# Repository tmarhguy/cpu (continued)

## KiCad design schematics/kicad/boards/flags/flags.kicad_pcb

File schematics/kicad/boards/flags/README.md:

# Flags Generation Board

**Comparison and status flag generation**

---

## Function

Generate 4 flags for ALU status and comparison:
- **LESS:** A < B (magnitude comparison)
- **EQUAL:** A == B (equality check)
- **POSITIVE:** OUT > 0 (positive result)
- **COUT:** Carry out (from adder)

---

## Schematic

*Flags generation circuit*

---

## Flag Implementations

### EQUAL Flag (~100T)

**Function:** Detect A == B

**Logic:**
```
EQUAL = ~((A[7] XOR B[7]) | (A[6] XOR B[6]) | ... | (A[0] XOR B[0]))
```

**Implementation:**
- 8× XOR gates (96T)
- 8-input NOR gate (16T)

### LESS Flag (~120T)

**Function:** Detect A < B

**Logic:** Cascaded priority comparison (MSB first)

**Implementation:** ~120T comparator logic

### POSITIVE Flag (~20T)

**Function:** Detect OUT > 0

**Logic:**
```
NOT_ZERO = OUT[7] | ... | OUT[0]
POSITIVE = ~OUT[7] & NOT_ZERO
```

### COUT Flag (0T)

**Function:** Pass carry from adder

**Implementation:** Direct wire

---

## Signals

**Inputs:**
- A[7:0], B[7:0] - For comparison
- OUT[7:0] - For POSITIVE detection
- COUT_IN - From adder

**Outputs:**
- LESS, EQUAL, POSITIVE, COUT

---

**Last Updated:** 2026-01-16

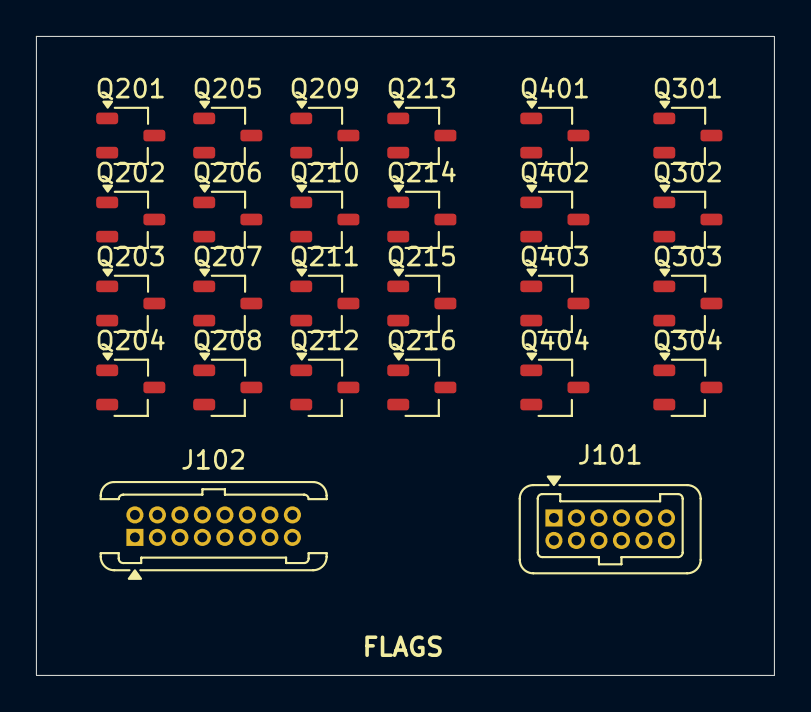
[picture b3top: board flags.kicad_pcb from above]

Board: 2 copper layers, 41.0 x 35.5 mm, 26 parts (0 on the bottom side), 23 nets, no tracks yet.

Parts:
J101: Conn_01x12_Pin; Harwin_Gecko-G125-FVX1205L0X_2x06_P1.25mm_Vertical
J102: Conn_01x16_Pin; Harwin_Gecko-G125-MVX1605L0X_2x08_P1.25mm_Vertical
Q201, Q210, Q211, Q212, Q213, Q214, Q215, Q216, Q301, Q304, Q401, Q404: NMOS; TSOT-23
Q202, Q203, Q204, Q205, Q206, Q207, Q208, Q209, Q302, Q303, Q402, Q403: PMOS; TSOT-23

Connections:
/SUM0: Q201.2 (G), Q202.2 (G)
/SUM1: Q203.2 (G), Q210.2 (G)
/SUM2: Q204.2 (G), Q211.2 (G)
/SUM3: Q205.2 (G), Q212.2 (G)
/SUM4: Q206.2 (G), Q213.2 (G)
/SUM5: Q207.2 (G), Q214.2 (G)
/SUM6: Q208.2 (G), Q215.2 (G)
/SUM7: Q209.2 (G), Q216.2 (G)
CMP0: Q301.1 (D), Q303.1 (D), Q304.1 (D), Q403.2 (G), Q404.2 (G)
CMP1: Q201.1 (D), Q209.1 (D), Q210.1 (D), Q211.1 (D), Q212.1 (D), Q213.1 (D), Q214.1 (D), Q215.1 (D), Q216.1 (D), Q301.2 (G), Q302.2 (G), Q401.2 (G), Q402.2 (G)
CMP2: Q401.1 (D), Q403.1 (D), Q404.1 (D)
CMP3: Q201.3 (S), Q210.3 (S), Q211.3 (S), Q212.3 (S), Q213.3 (S), Q214.3 (S), Q215.3 (S), Q216.3 (S), Q301.3 (S), Q304.3 (S), Q401.3 (S), Q404.3 (S)
C_OUT: Q303.2 (G), Q304.2 (G)
unnamed: Q202.1 (D), Q203.3 (S)
unnamed: Q203.1 (D), Q204.3 (S)
unnamed: Q204.1 (D), Q205.3 (S)
unnamed: Q205.1 (D), Q206.3 (S)
unnamed: Q206.1 (D), Q207.3 (S)
unnamed: Q207.1 (D), Q208.3 (S)
unnamed: Q208.1 (D), Q209.3 (S)
unnamed: Q302.1 (D), Q303.3 (S)
unnamed: Q402.1 (D), Q403.3 (S)
VCC: Q202.3 (S), Q302.3 (S), Q402.3 (S)

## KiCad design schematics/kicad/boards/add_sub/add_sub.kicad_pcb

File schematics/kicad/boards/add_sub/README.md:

# Add/Subtract Module

**8-bit adder with conditional B inversion for subtraction**

---

## Function

Implements both addition and subtraction using a single 8-bit ripple-carry adder.

**Operations:**
- ADD: OUT = A + B (when M=0)
- SUB: OUT = A - B (when M=1, using 2's complement)

---

## Block Diagram

```
A[7:0] ────────────────┐
                       ├──> Full Adder (8-bit) ──> SUM[7:0]
B[7:0] ──> XOR[M] ─────┤
                       │
M ──────────────> Cin ─┘
```

---

## Implementation

### XOR Array (96T)

**Purpose:** Conditional B inversion

```
B'[i] = B[i] XOR M  (for i = 0 to 7)
```

**Truth table:**
| M | B | B' |
|---|---|----|
| 0 | 0 | 0 |
| 0 | 1 | 1 |
| 1 | 0 | 1 |
| 1 | 1 | 0 |

When M=0 (ADD): B' = B  
When M=1 (SUB): B' = ~B

### 8-Bit Ripple-Carry Adder (336T)

**Structure:** 8 cascaded full adders

**Per full adder (42T):**
- Sum = A ⊕ B' ⊕ Cin
- Cout = A·B' + Cin·(A ⊕ B')

---

## Schematic

*Complete add/subtract module schematic*

> **Evidence:** Schematic shows XOR array and 8-bit adder.

---

## PCB

*Fabricated add/subtract board*

> **Evidence:** Physical implementation of arithmetic unit.

---

## Signals

### Inputs

| Signal | Width | Voltage | Description |
|--------|-------|---------|-------------|
| A[7:0] | 8 bits | 0V/5V | First operand |
| B[7:0] | 8 bits | 0V/5V | Second operand |
| M | 1 bit | 0V/5V | ADD(0) or SUB(1) mode |
| VCC | Power | 5V | Power supply |
| GND | Power | 0V | Ground |

### Outputs

| Signal | Width | Voltage | Description |
|--------|-------|---------|-------------|
| SUM[7:0] | 8 bits | 0V/5V | Arithmetic result |
| COUT | 1 bit | 0V/5V | Carry out (unsigned overflow) |

---

## Timing

**Propagation delay:**
- XOR array: ~15ns
- Adder (worst case): ~400ns
- **Total:** ~415ns (input to output)

**Critical path:** A[0] → XOR → FA0 → FA1 → ... → FA7 → SUM[7]

---

## Testing

**Test vectors:**

| A | B | M | Expected SUM | Expected COUT |
|---|---|---|--------------|---------------|
| 0x01 | 0x01 | 0 | 0x02 | 0 |
| 0xFF | 0x01 | 0 | 0x00 | 1 |
| 0x64 | 0x23 | 1 | 0x41 | 1 |
| 0x00 | 0x01 | 1 | 0xFF | 0 |

---

**Last Updated:** 2026-01-16

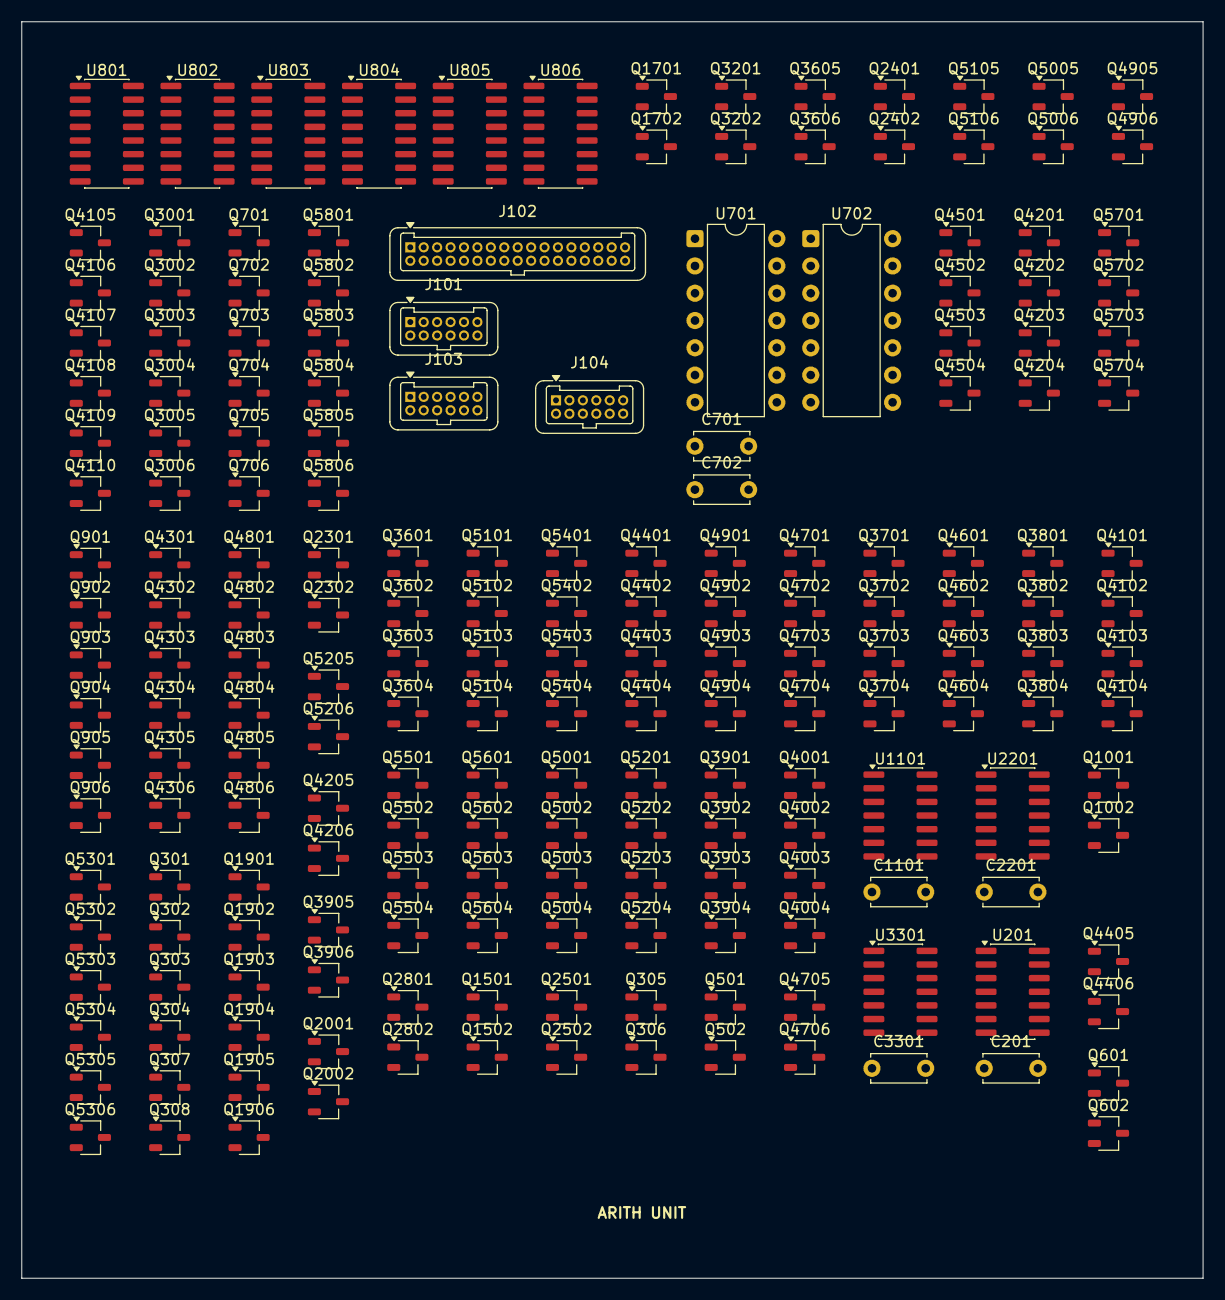
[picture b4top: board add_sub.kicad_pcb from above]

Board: 2 copper layers, 110.0 x 117.0 mm, 200 parts (0 on the bottom side), 148 nets, no tracks yet.

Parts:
C201, C701, C702, C1101, C2201, C3301: 100nF; C_Disc_D5.0mm_W2.5mm_P5.00mm
J101, J103, J104: Conn_01x12_Pin; Harwin_Gecko-G125-FVX1205L0X_2x06_P1.25mm_Vertical
J102: Conn_01x34_Pin; Harwin_Gecko-G125-FVX3405L0X_2x17_P1.25mm_Vertical
Q301, Q304, Q306, Q308, Q502, Q602, Q701, Q704, Q706, Q901, Q904, Q906, Q1002, Q1502, Q1702, Q1901, Q1904, Q1906, Q2002, Q2302, Q2402, Q2502, Q2802, Q3001, Q3004, Q3006, Q3202, Q3602, Q3603, Q3606, Q3702, Q3703, Q3802, Q3803, Q3902, Q3903, Q3906, Q4002, Q4003, Q4102, Q4103, Q4105, Q4108, Q4110, Q4202, Q4203, Q4206, Q4301, Q4304, Q4306, Q4402, Q4403, Q4406, Q4502, Q4503, Q4602, Q4603, Q4702, Q4703, Q4706, Q4801, Q4804, Q4806, Q4902, Q4903, Q4906, Q5002, Q5003, Q5006, Q5102, Q5103, Q5106, Q5202, Q5203, Q5206, Q5301, Q5304, Q5306, Q5402, Q5403, Q5502, Q5503, Q5602, Q5603, Q5702, Q5703, Q5801, Q5804, Q5806: NMOS; TSOT-23
Q302, Q303, Q305, Q307, Q501, Q601, Q702, Q703, Q705, Q902, Q903, Q905, Q1001, Q1501, Q1701, Q1902, Q1903, Q1905, Q2001, Q2301, Q2401, Q2501, Q2801, Q3002, Q3003, Q3005, Q3201, Q3601, Q3604, Q3605, Q3701, Q3704, Q3801, Q3804, Q3901, Q3904, Q3905, Q4001, Q4004, Q4101, Q4104, Q4106, Q4107, Q4109, Q4201, Q4204, Q4205, Q4302, Q4303, Q4305, Q4401, Q4404, Q4405, Q4501, Q4504, Q4601, Q4604, Q4701, Q4704, Q4705, Q4802, Q4803, Q4805, Q4901, Q4904, Q4905, Q5001, Q5004, Q5005, Q5101, Q5104, Q5105, Q5201, Q5204, Q5205, Q5302, Q5303, Q5305, Q5401, Q5404, Q5501, Q5504, Q5601, Q5604, Q5701, Q5704, Q5802, Q5803, Q5805: PMOS; TSOT-23
U201, U1101, U2201, U3301: 74HC86; SOIC-14_3.9x8.7mm_P1.27mm
U701, U702: 74HC86; DIP-14_W7.62mm
U801, U802, U803, U804, U805, U806: 74HC157; SOIC-16_3.9x9.9mm_P1.27mm

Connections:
/4to1mux1/B0: U801.3 (I1a), U801.6 (I1b), U801.10 (I1c), U801.13 (I1d), U802.3 (I1a), U802.6 (I1b), U802.10 (I1c)
/4to1mux1/Y0: U701.1, U805.4 (Za)
/4to1mux1/Y1: U701.4, U805.7 (Zb)
/4to1mux1/Y2: U701.9, U805.9 (Zc)
/4to1mux1/Y3: U701.12, U805.12 (Zd)
/4to1mux1/Y4: U702.1, U806.4 (Za)
/4to1mux1/Y5: U702.4, U806.7 (Zb)
/4to1mux1/Y6: U702.9, U806.9 (Zc)
/4to1mux1/Y7: U702.12, U806.12 (Zd)
/B_SEL0: Q4705.1 (D), Q4706.1 (D), U805.1 (S), U806.1 (S)
/B_SEL1: Q5205.1 (D), Q5206.1 (D), U801.1 (S), U802.1 (S), U803.1 (S), U804.1 (S)
/CTRL0: Q903.2 (G), Q904.2 (G), Q3801.2 (G), Q3803.2 (G), Q5105.2 (G), Q5106.2 (G)
/CTRL1: Q303.2 (G), Q304.2 (G), Q3601.2 (G), Q3603.2 (G)
/CTRL2: Q4905.2 (G), Q4906.2 (G)
/CTRL4: Q901.2 (G), Q902.2 (G)
/C_IN: Q307.1 (D), Q308.1 (D), Q3901.2 (G), Q3903.2 (G), U201.5
/M: Q301.2 (G), Q302.2 (G), Q905.1 (D), Q906.1 (D), U701.2, U701.5, U701.10, U701.13, U702.2, U702.5, U702.10, U702.13
/adder8/B0: Q4002.2 (G), Q4004.2 (G), U201.2, U701.3
/adder8/B1: Q4202.2 (G), Q4204.2 (G), U201.10, U701.6
/adder8/B2: Q4502.2 (G), Q4504.2 (G), U701.8, U1101.2
/adder8/B3: Q4702.2 (G), Q4704.2 (G), U701.11, U1101.10
/adder8/B4: Q5002.2 (G), Q5004.2 (G), U702.3, U2201.2
/adder8/B5: Q5202.2 (G), Q5204.2 (G), U702.6, U2201.10
/adder8/B6: Q5502.2 (G), Q5504.2 (G), U702.8, U3301.2
/adder8/B7: Q5702.2 (G), Q5704.2 (G), U702.11, U3301.10
/adder8/adder2_1/C_OUT: Q4305.1 (D), Q4306.1 (D), Q4401.2 (G), Q4403.2 (G), U1101.5
/adder8/adder2_1/and2_1/B: Q3902.2 (G), Q3904.2 (G), U201.3, U201.4
/adder8/adder2_1/and2_1/Y: Q305.1 (D), Q306.1 (D), Q701.2 (G), Q702.2 (G)
/adder8/adder2_1/and2_1/nand2_1/Y: Q305.2 (G), Q306.2 (G), Q3901.1 (D), Q3902.1 (D), Q3904.1 (D)
/adder8/adder2_1/and2_2/Y: Q703.2 (G), Q704.2 (G), Q1001.1 (D), Q1002.1 (D)
/adder8/adder2_1/and2_2/nand2_1/Y: Q1001.2 (G), Q1002.2 (G), Q4001.1 (D), Q4002.1 (D), Q4004.1 (D)
/adder8/adder2_1/and2_3/A: Q705.1 (D), Q706.1 (D), Q4101.2 (G), Q4103.2 (G), U201.13
/adder8/adder2_1/and2_3/B: Q4102.2 (G), Q4104.2 (G), U201.8, U201.12
/adder8/adder2_1/and2_3/Y: Q501.1 (D), Q502.1 (D)
/adder8/adder2_1/and2_3/nand2_1/Y: Q501.2 (G), Q502.2 (G), Q4101.1 (D), Q4102.1 (D), Q4104.1 (D)
/adder8/adder2_1/and2_4/Y: Q601.1 (D), Q602.1 (D), Q4303.2 (G), Q4304.2 (G)
/adder8/adder2_1/and2_4/nand2_1/Y: Q601.2 (G), Q602.2 (G), Q4201.1 (D), Q4202.1 (D), Q4204.1 (D)
/adder8/adder2_1/or2_2/A: Q4301.2 (G), Q4302.2 (G)
/adder8/adder2_2/C_OUT: Q4805.1 (D), Q4806.1 (D), Q4901.2 (G), Q4903.2 (G), U2201.5
/adder8/adder2_2/and2_1/B: Q4402.2 (G), Q4404.2 (G), U1101.3, U1101.4
/adder8/adder2_2/and2_1/Y: Q1701.1 (D), Q1702.1 (D), Q1901.2 (G), Q1902.2 (G)
/adder8/adder2_2/and2_1/nand2_1/Y: Q1701.2 (G), Q1702.2 (G), Q4401.1 (D), Q4402.1 (D), Q4404.1 (D)
/adder8/adder2_2/and2_2/Y: Q1501.1 (D), Q1502.1 (D), Q1903.2 (G), Q1904.2 (G)
/adder8/adder2_2/and2_2/nand2_1/Y: Q1501.2 (G), Q1502.2 (G), Q4501.1 (D), Q4502.1 (D), Q4504.1 (D)
/adder8/adder2_2/and2_3/A: Q1905.1 (D), Q1906.1 (D), Q4601.2 (G), Q4603.2 (G), U1101.13
/adder8/adder2_2/and2_3/B: Q4602.2 (G), Q4604.2 (G), U1101.8, U1101.12
/adder8/adder2_2/and2_3/Y: Q2501.1 (D), Q2502.1 (D)
/adder8/adder2_2/and2_3/nand2_1/Y: Q2501.2 (G), Q2502.2 (G), Q4601.1 (D), Q4602.1 (D), Q4604.1 (D)
/adder8/adder2_2/and2_4/Y: Q2301.1 (D), Q2302.1 (D), Q4803.2 (G), Q4804.2 (G)
/adder8/adder2_2/and2_4/nand2_1/Y: Q2301.2 (G), Q2302.2 (G), Q4701.1 (D), Q4702.1 (D), Q4704.1 (D)
/adder8/adder2_2/or2_2/A: Q4801.2 (G), Q4802.2 (G)
/adder8/adder2_3/C_OUT: Q5305.1 (D), Q5306.1 (D), Q5401.2 (G), Q5403.2 (G), U3301.5
/adder8/adder2_3/and2_1/B: Q4902.2 (G), Q4904.2 (G), U2201.3, U2201.4
/adder8/adder2_3/and2_1/Y: Q2801.1 (D), Q2802.1 (D), Q3001.2 (G), Q3002.2 (G)
/adder8/adder2_3/and2_1/nand2_1/Y: Q2801.2 (G), Q2802.2 (G), Q4901.1 (D), Q4902.1 (D), Q4904.1 (D)
/adder8/adder2_3/and2_2/Y: Q2001.1 (D), Q2002.1 (D), Q3003.2 (G), Q3004.2 (G)
/adder8/adder2_3/and2_2/nand2_1/Y: Q2001.2 (G), Q2002.2 (G), Q5001.1 (D), Q5002.1 (D), Q5004.1 (D)
/adder8/adder2_3/and2_3/A: Q3005.1 (D), Q3006.1 (D), Q5101.2 (G), Q5103.2 (G), U2201.13
/adder8/adder2_3/and2_3/B: Q5102.2 (G), Q5104.2 (G), U2201.8, U2201.12
/adder8/adder2_3/and2_3/Y: Q3201.1 (D), Q3202.1 (D)
/adder8/adder2_3/and2_3/nand2_1/Y: Q3201.2 (G), Q3202.2 (G), Q5101.1 (D), Q5102.1 (D), Q5104.1 (D)
/adder8/adder2_3/and2_4/Y: Q4205.1 (D), Q4206.1 (D), Q5303.2 (G), Q5304.2 (G)
/adder8/adder2_3/and2_4/nand2_1/Y: Q4205.2 (G), Q4206.2 (G), Q5201.1 (D), Q5202.1 (D), Q5204.1 (D)
/adder8/adder2_3/or2_2/A: Q5301.2 (G), Q5302.2 (G)
/adder8/adder2_4/and2_1/B: Q5402.2 (G), Q5404.2 (G), U3301.3, U3301.4
/adder8/adder2_4/and2_1/Y: Q3905.1 (D), Q3906.1 (D), Q4105.2 (G), Q4106.2 (G)
/adder8/adder2_4/and2_1/nand2_1/Y: Q3905.2 (G), Q3906.2 (G), Q5401.1 (D), Q5402.1 (D), Q5404.1 (D)
/adder8/adder2_4/and2_2/Y: Q2401.1 (D), Q2402.1 (D), Q4107.2 (G), Q4108.2 (G)
/adder8/adder2_4/and2_2/nand2_1/Y: Q2401.2 (G), Q2402.2 (G), Q5501.1 (D), Q5502.1 (D), Q5504.1 (D)
/adder8/adder2_4/and2_3/A: Q4109.1 (D), Q4110.1 (D), Q5601.2 (G), Q5603.2 (G), U3301.13
/adder8/adder2_4/and2_3/B: Q5602.2 (G), Q5604.2 (G), U3301.8, U3301.12
/adder8/adder2_4/and2_3/Y: Q3605.1 (D), Q3606.1 (D)
/adder8/adder2_4/and2_3/nand2_1/Y: Q3605.2 (G), Q3606.2 (G), Q5601.1 (D), Q5602.1 (D), Q5604.1 (D)
/adder8/adder2_4/and2_4/Y: Q4405.1 (D), Q4406.1 (D), Q5803.2 (G), Q5804.2 (G)
/adder8/adder2_4/and2_4/nand2_1/Y: Q4405.2 (G), Q4406.2 (G), Q5701.1 (D), Q5702.1 (D), Q5704.1 (D)
/adder8/adder2_4/or2_2/A: Q5801.2 (G), Q5802.2 (G)
/and2_1/A: Q3701.2 (G), Q3703.2 (G), Q5105.1 (D), Q5106.1 (D)
/and2_1/B: Q3702.2 (G), Q3704.2 (G), Q3802.2 (G), Q3804.2 (G), Q5005.1 (D), Q5006.1 (D)
/and2_1/nand2_1/Y: Q3701.1 (D), Q3702.1 (D), Q3704.1 (D), Q5205.2 (G), Q5206.2 (G)
/and2_2/nand2_1/Y: Q3801.1 (D), Q3802.1 (D), Q3804.1 (D), Q4705.2 (G), Q4706.2 (G)
/and2_3/B: Q3602.2 (G), Q3604.2 (G), Q4905.1 (D), Q4906.1 (D)
/and2_3/nand2_1/Y: Q3601.1 (D), Q3602.1 (D), Q3604.1 (D), Q5005.2 (G), Q5006.2 (G)
A0: Q4001.2 (G), Q4003.2 (G), U201.1
A1: Q4201.2 (G), Q4203.2 (G), U201.9
A2: Q4501.2 (G), Q4503.2 (G), U1101.1
A3: Q4701.2 (G), Q4703.2 (G), U1101.9
A4: Q5001.2 (G), Q5003.2 (G), U2201.1
A5: Q5201.2 (G), Q5203.2 (G), U2201.9
A6: Q5501.2 (G), Q5503.2 (G), U3301.1
A7: Q5701.2 (G), Q5703.2 (G), U3301.9
C_OUT: Q5805.1 (D), Q5806.1 (D)
GND: C201.2, C701.2, C702.2, C1101.2, C2201.2, C3301.2, Q301.3 (S), Q304.3 (S), Q306.3 (S), Q308.3 (S), Q502.3 (S), Q602.3 (S), Q701.3 (S), Q704.3 (S), Q706.3 (S), Q901.3 (S), Q904.3 (S), Q906.3 (S), Q1002.3 (S), Q1502.3 (S), Q1702.3 (S), Q1901.3 (S), Q1904.3 (S), Q1906.3 (S), Q2002.3 (S), Q2302.3 (S), Q2402.3 (S), Q2502.3 (S), Q2802.3 (S), Q3001.3 (S), Q3004.3 (S), Q3006.3 (S), Q3202.3 (S), Q3603.3 (S), Q3606.3 (S), Q3703.3 (S), Q3803.3 (S), Q3903.3 (S), Q3906.3 (S), Q4003.3 (S), Q4103.3 (S), Q4105.3 (S), Q4108.3 (S), Q4110.3 (S), Q4203.3 (S), Q4206.3 (S), Q4301.3 (S), Q4304.3 (S), Q4306.3 (S), Q4403.3 (S), Q4406.3 (S), Q4503.3 (S), Q4603.3 (S), Q4703.3 (S), Q4706.3 (S), Q4801.3 (S), Q4804.3 (S), Q4806.3 (S), Q4903.3 (S), Q4906.3 (S), Q5003.3 (S), Q5006.3 (S), Q5103.3 (S), Q5106.3 (S), Q5203.3 (S), Q5206.3 (S), Q5301.3 (S), Q5304.3 (S), Q5306.3 (S), Q5403.3 (S), Q5503.3 (S), Q5603.3 (S), Q5703.3 (S), Q5801.3 (S), Q5804.3 (S), Q5806.3 (S), U201.7 (GND), U701.7 (GND), U702.7 (GND), U801.8 (GND), U801.15 (E), U802.8 (GND), U802.15 (E), U803.2 (I0a), U803.3 (I1a), U803.5 (I0b), U803.6 (I1b), U803.8 (GND), U803.10 (I1c), U803.11 (I0c), U803.13 (I1d), U803.14 (I0d), U803.15 (E), U804.2 (I0a), U804.3 (I1a), U804.5 (I0b), U804.6 (I1b), U804.8 (GND), U804.10 (I1c), U804.11 (I0c), U804.13 (I1d), U804.14 (I0d), U804.15 (E), U805.8 (GND), U805.15 (E), U806.8 (GND), U806.15 (E), U1101.7 (GND), U2201.7 (GND), U3301.7 (GND)
unnamed: Q301.1 (D), Q303.1 (D), Q304.1 (D), Q307.2 (G), Q308.2 (G)
unnamed: Q302.1 (D), Q303.3 (S)
unnamed: Q701.1 (D), Q703.1 (D), Q704.1 (D), Q705.2 (G), Q706.2 (G)
unnamed: Q702.1 (D), Q703.3 (S)
unnamed: Q901.1 (D), Q903.1 (D), Q904.1 (D), Q905.2 (G), Q906.2 (G)
unnamed: Q902.1 (D), Q903.3 (S)
unnamed: Q1901.1 (D), Q1903.1 (D), Q1904.1 (D), Q1905.2 (G), Q1906.2 (G)
unnamed: Q1902.1 (D), Q1903.3 (S)
unnamed: Q3001.1 (D), Q3003.1 (D), Q3004.1 (D), Q3005.2 (G), Q3006.2 (G)
unnamed: Q3002.1 (D), Q3003.3 (S)
unnamed: Q3602.3 (S), Q3603.1 (D)
unnamed: Q3702.3 (S), Q3703.1 (D)
unnamed: Q3802.3 (S), Q3803.1 (D)
unnamed: Q3902.3 (S), Q3903.1 (D)
unnamed: Q4002.3 (S), Q4003.1 (D)
unnamed: Q4102.3 (S), Q4103.1 (D)
unnamed: Q4105.1 (D), Q4107.1 (D), Q4108.1 (D), Q4109.2 (G), Q4110.2 (G)
unnamed: Q4106.1 (D), Q4107.3 (S)
unnamed: Q4202.3 (S), Q4203.1 (D)
unnamed: Q4301.1 (D), Q4303.1 (D), Q4304.1 (D), Q4305.2 (G), Q4306.2 (G)
unnamed: Q4302.1 (D), Q4303.3 (S)
unnamed: Q4402.3 (S), Q4403.1 (D)
unnamed: Q4502.3 (S), Q4503.1 (D)
unnamed: Q4602.3 (S), Q4603.1 (D)
unnamed: Q4702.3 (S), Q4703.1 (D)
unnamed: Q4801.1 (D), Q4803.1 (D), Q4804.1 (D), Q4805.2 (G), Q4806.2 (G)
unnamed: Q4802.1 (D), Q4803.3 (S)
unnamed: Q4902.3 (S), Q4903.1 (D)
unnamed: Q5002.3 (S), Q5003.1 (D)
unnamed: Q5102.3 (S), Q5103.1 (D)
unnamed: Q5202.3 (S), Q5203.1 (D)
unnamed: Q5301.1 (D), Q5303.1 (D), Q5304.1 (D), Q5305.2 (G), Q5306.2 (G)
unnamed: Q5302.1 (D), Q5303.3 (S)
unnamed: Q5402.3 (S), Q5403.1 (D)
unnamed: Q5502.3 (S), Q5503.1 (D)
unnamed: Q5602.3 (S), Q5603.1 (D)
unnamed: Q5702.3 (S), Q5703.1 (D)
unnamed: Q5801.1 (D), Q5803.1 (D), Q5804.1 (D), Q5805.2 (G), Q5806.2 (G)
unnamed: Q5802.1 (D), Q5803.3 (S)
unnamed: U801.4 (Za), U805.2 (I0a)
unnamed: U801.7 (Zb), U805.5 (I0b)
unnamed: U801.9 (Zc), U805.11 (I0c)
unnamed: U801.12 (Zd), U805.14 (I0d)
unnamed: U802.4 (Za), U805.3 (I1a)
unnamed: U802.7 (Zb), U805.6 (I1b)
unnamed: U802.9 (Zc), U805.10 (I1c)
unnamed: U802.12 (Zd), U805.13 (I1d)
unnamed: U803.4 (Za), U806.2 (I0a)
unnamed: U803.7 (Zb), U806.5 (I0b)
unnamed: U803.9 (Zc), U806.11 (I0c)
unnamed: U803.12 (Zd), U806.14 (I0d)
unnamed: U804.4 (Za), U806.3 (I1a)
unnamed: U804.7 (Zb), U806.6 (I1b)
unnamed: U804.9 (Zc), U806.10 (I1c)
unnamed: U804.12 (Zd), U806.13 (I1d)
VCC: C201.1, C701.1, C702.1, C1101.1, C2201.1, C3301.1, Q302.3 (S), Q305.3 (S), Q307.3 (S), Q501.3 (S), Q601.3 (S), Q702.3 (S), Q705.3 (S), Q902.3 (S), Q905.3 (S), Q1001.3 (S), Q1501.3 (S), Q1701.3 (S), Q1902.3 (S), Q1905.3 (S), Q2001.3 (S), Q2301.3 (S), Q2401.3 (S), Q2501.3 (S), Q2801.3 (S), Q3002.3 (S), Q3005.3 (S), Q3201.3 (S), Q3601.3 (S), Q3604.3 (S), Q3605.3 (S), Q3701.3 (S), Q3704.3 (S), Q3801.3 (S), Q3804.3 (S), Q3901.3 (S), Q3904.3 (S), Q3905.3 (S), Q4001.3 (S), Q4004.3 (S), Q4101.3 (S), Q4104.3 (S), Q4106.3 (S), Q4109.3 (S), Q4201.3 (S), Q4204.3 (S), Q4205.3 (S), Q4302.3 (S), Q4305.3 (S), Q4401.3 (S), Q4404.3 (S), Q4405.3 (S), Q4501.3 (S), Q4504.3 (S), Q4601.3 (S), Q4604.3 (S), Q4701.3 (S), Q4704.3 (S), Q4705.3 (S), Q4802.3 (S), Q4805.3 (S), Q4901.3 (S), Q4904.3 (S), Q4905.3 (S), Q5001.3 (S), Q5004.3 (S), Q5005.3 (S), Q5101.3 (S), Q5104.3 (S), Q5105.3 (S), Q5201.3 (S), Q5204.3 (S), Q5205.3 (S), Q5302.3 (S), Q5305.3 (S), Q5401.3 (S), Q5404.3 (S), Q5501.3 (S), Q5504.3 (S), Q5601.3 (S), Q5604.3 (S), Q5701.3 (S), Q5704.3 (S), Q5802.3 (S), Q5805.3 (S), U201.14 (VCC), U701.14 (VCC), U702.14 (VCC), U801.16 (VCC), U802.13 (I1d), U802.16 (VCC), U803.16 (VCC), U804.16 (VCC), U805.16 (VCC), U806.16 (VCC), U1101.14 (VCC), U2201.14 (VCC), U3301.14 (VCC)

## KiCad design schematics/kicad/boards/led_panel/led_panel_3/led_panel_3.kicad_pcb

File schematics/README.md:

# Schematics & PCB Design

**Hardware design files for the 8-Bit Transistor CPU**

This directory contains all schematic captures, PCB layouts, and hardware design files for the complete ALU system.

---

## Contents

```
schematics/
├── kicad/                  # KiCad PCB design files
│   ├── main_logic/        # Main ALU logic board
│   ├── add_sub/           # Add/Subtract unit
│   ├── flags/             # Flag generation circuit
│   ├── main_control/      # Control unit
│   └── led_panels/        # Display panels (4x)
├── ltspice/               # SPICE simulation files
│   ├── models/            # MOSFET models
│   └── runs/              # Simulation outputs
├── web/                   # 3D models and exports
│   └── glb exports/       # GLB 3D models
└── README.md              # This file
```

---

## Overview

This directory contains:
- **KiCad schematics** - Complete circuit diagrams
- **PCB layouts** - Manufacturable board designs
- **SPICE simulations** - Transistor-level verification
- **3D models** - Visualization and mechanical design
- **Gerber files** - Manufacturing outputs

---

## KiCad Projects

### Main System Boards

| Board | Purpose | Transistors | Size | Status |
|-------|---------|-------------|------|--------|
| **Main ALU** | Core ALU (arithmetic + logic) | 3,856+ | 270×270mm | Complete |
| **Flags** | Flag generation (LESS, EQUAL, POSITIVE, COUT) | ~240 | Integrated | Complete |
| **Control** | Opcode decoder & control signals | ~100 | Integrated | Complete |
| **LED Panels** | 8-bit output displays | N/A | Separate | Complete |

**Note:** Main ALU is a single 270mm × 270mm combinational circuit board

### Main Logic Board

**File:** `kicad/main_logic/main_logic.kicad_sch`

*Main ALU logic board schematic*

**Components:**
- 8-bit ripple-carry adder
- Logic unit (NAND, NOR, XOR arrays)
- 2-to-1 multiplexer (74HC157)
- Global inverter array
- Power distribution

*Fabricated main logic PCB*

**Evidence:** Complete schematic and fabricated PCB for main ALU core.

### Add/Sub Unit

**File:** `kicad/add_sub/add_sub.kicad_sch`

*Add/Subtract unit schematic*

**Components:**
- XOR array for B input conditioning
- Carry-in control
- Mode selection logic

*Fabricated add/sub PCB*

**Evidence:** XOR array implementation for efficient ADD/SUB operation.

### Flags Circuit

**File:** `kicad/flags/flags.kicad_sch`

*Flags generation circuit schematic*

**Components:**
- 8-input NOR for Zero flag
- MSB connection for Negative flag
- Carry-out for Carry flag
- XOR logic for Overflow flag

*Fabricated flags PCB*

**Evidence:** Flag generation circuit implements standard ALU status indicators.

### Control Unit

**File:** `kicad/main_control/main_control.kicad_sch`

*Control unit schematic*

**Components:**
- Opcode decoder
- Control signal generation
- Arduino interface
- Load signal distribution

*Fabricated control PCB*

**Evidence:** Control unit decodes 4-bit opcode into internal control signals.

### LED Display Panels

**Files:** `kicad/led_panels/led_panel_[1-4]/`

*LED display panel 1 schematic*

**Components:**
- 8× LEDs with current-limiting resistors
- Buffer drivers
- Power distribution

*Fabricated LED display panels*

**Evidence:** LED panels provide visual output for 8-bit results.

---

## PCB Design Process

### Phase 1: Schematic Capture

*ALU schematic capture in KiCad*

**Steps:**
1. Create hierarchical schematic
2. Place components
3. Wire connections
4. Add power symbols
5. Annotate references
6. Run electrical rules check (ERC)

### Phase 2: PCB Layout

*ALU PCB layout in KiCad*

**Steps:**
1. Import netlist from schematic
2. Place components
3. Define board outline
4. Route traces
5. Add ground planes
6. Run design rules check (DRC)

### Phase 3: Pre-Routing

*Unrouted PCB showing component placement and ratsnest*

**Ratsnest view shows:**
- Component placement
- Required connections
- Routing complexity
- Potential issues

### Phase 4: Routing

*Click to watch: PCB routing demonstration*

**Routing strategy:**
- Power and ground first
- Critical signals next
- Minimize vias
- Avoid acute angles
- Maintain trace spacing

*Click to watch: Complete KiCad routing tutorial*

**Evidence:** Routing videos demonstrate systematic PCB layout approach.

### Phase 5: 3D Visualization

*3D render of complete ALU system*

**3D models available:**
- Main logic board
- Control unit
- Flags circuit
- LED panels

See [web/README.md](../web/README.md) for 3D model exports.

---

## Component Library

### Logic Gates

All gates are implemented using discrete transistors (NMOS + PMOS pairs).

| Gate | Schematic | Transistors | Implementation |
|------|-----------|-------------|----------------|
| NOT | `gate_inv_1bit` | 2T | 1 PMOS + 1 NMOS |
| NAND | `gate_nand_2in` | 4T | 2 PMOS parallel + 2 NMOS series |
| NOR | `gate_nor_2in` | 4T | 2 PMOS series + 2 NMOS parallel |
| AND | `gate_and_2in` | 6T | NAND + NOT |
| OR | `gate_or_2in` | 6T | NOR + NOT |
| XOR | `gate_xor_2in` | 12T | Complex CMOS |
| XNOR | `gate_xnor_2in` | 12T | XOR + NOT |

*2-input AND gate schematic*

### Arithmetic Components

| Component | Schematic | Description |
|-----------|-----------|-------------|
| Half Adder | `half_adder` | Sum and carry from 2 inputs |
| Full Adder | `full_adder` | Sum and carry from 3 inputs |
| 2-bit Adder | `adder2` | Ripple-carry 2-bit adder |
| 8-bit Adder | `adder8` | Complete 8-bit ripple-carry |

*8-bit ripple-carry adder schematic*

### Multiplexers

| Component | Schematic | Description |
|-----------|-----------|-------------|
| 2-to-1 MUX | `mux_2to1_8bit` | Select between two 8-bit inputs |
| 4-to-1 MUX | `mux_4to1_8bit` | Select between four 8-bit inputs |
| 8-to-1 MUX | `mux_8to1_8bit` | Select between eight 8-bit inputs |

*8-bit 2-to-1 multiplexer schematic*

---

## SPICE Simulations

### Simulation Directory

**Location:** `schematics/ltspice/`

**Contents:**
- MOSFET models (`.lib` files)
- Circuit netlists (`.cir` files)
- Simulation outputs (waveforms, logs)

### Gate-Level Simulations

All primitive gates verified through SPICE simulation.

#### Inverter (NOT Gate)

*NOT gate transient analysis showing input/output inversion*

**Verification:**
- Output inverts input
- VOH ≈ 5V, VOL ≈ 0V
- Propagation delay < 10ns

#### Full Adder

*Full adder SPICE simulation showing sum and carry outputs*

**Verification:**
- All 8 input combinations correct
- Sum = A ⊕ B ⊕ Cin
- Cout = AB + Cin(A ⊕ B)

**Evidence:** SPICE simulations validate transistor-level correctness before fabrication.

### Running SPICE Simulations

```bash
cd schematics/ltspice

# Run a simulation
ngspice inverter.cir

# In ngspice prompt
ngspice> run
ngspice> plot v(in) v(out)
ngspice> quit
```

See [ltspice/README.md](ltspice/README.md) for detailed simulation guide.

---

## Fabrication

### PCB Manufacturing

**Manufacturer:** JLCPCB, PCBWay

**Specifications:**
- **Board size:** 270mm × 270mm (10.6" × 10.6")
- **Layers:** 2 (top + bottom)
- **Material:** FR-4
- **Thickness:** 1.6mm
- **Copper weight:** 1 oz (35 µm)
- **Surface finish:** HASL (lead-free)
- **Silkscreen:** White on green solder mask
- **Min trace/space:** 0.2mm / 0.2mm
- **Min drill:** 0.3mm

**Note:** Large format PCB required for 3,856+ discrete transistors

### Component Sourcing

**Suppliers:**
- **Transistors:** DigiKey, Mouser
- **Resistors/Capacitors:** LCSC, DigiKey
- **ICs (74HC):** DigiKey, Mouser
- **LEDs:** LCSC, DigiKey
- **Connectors:** DigiKey, Mouser

### Bill of Materials

See [docs/build-notes/bom.md](../docs/build-notes/bom.md) for complete BOM.

**Key components:**
- 3,856+ discrete transistors (NMOS + PMOS)
- 74HC574 octal D flip-flops (3×)
- 74HC157 quad 2-to-1 multiplexers (2×)
- Resistors, capacitors, LEDs
- Headers and connectors

---

## Assembly

### Assembly Process

*Initial component placement before soldering*

*Soldering in progress*

*Completed board assembly*

**Assembly steps:**
1. Inspect PCB for defects
2. Solder smallest components first (resistors, capacitors)
3. Solder transistors
4. Solder ICs (use sockets recommended)
5. Solder headers and connectors
6. Visual inspection
7. Continuity testing
8. Power-on test

**Evidence:** Assembly photos document the complete build process.

### Soldering Tips

- **Temperature:** 300-350°C for lead-free solder
- **Tip:** Use fine chisel tip for precision
- **Flux:** Apply flux for better solder flow
- **Inspection:** Use magnification to check joints
- **Testing:** Test each board before integration

---

## Design Files

### KiCad Files

| File Type | Extension | Purpose |
|-----------|-----------|---------|
| Project | `.kicad_pro` | Project settings |
| Schematic | `.kicad_sch` | Circuit diagram |
| PCB | `.kicad_pcb` | Board layout |
| Symbol Library | `.kicad_sym` | Custom symbols |
| Footprint Library | `.kicad_mod` | Custom footprints |

### Export Formats

| Format | Purpose | Location |
|--------|---------|----------|
| **PDF** | Documentation | `schematics photos jpg/` |
| **SVG** | Vector graphics | `schematics photos svg/` |
| **Gerber** | Manufacturing | `gerber/` (if exists) |
| **BOM** | Component list | `docs/build-notes/bom.md` |
| **3D (STEP)** | Mechanical | `web/glb exports/` |

---

## Design Guidelines

### Schematic Best Practices

1. **Hierarchical Design:**
   - Use hierarchical sheets for complex circuits
   - Create reusable subcircuits
   - Maintain clear hierarchy

2. **Labeling:**
   - Label all nets clearly
   - Use consistent naming convention
   - Add component values

3. **Documentation:**
   - Add notes for complex logic
   - Include design rationale
   - Reference datasheets

### PCB Best Practices

1. **Layout:**
   - Group related components
   - Minimize trace lengths
   - Consider signal integrity

2. **Power Distribution:**
   - Use wide traces for power
   - Add decoupling capacitors (100nF per IC)
   - Implement ground planes

3. **Manufacturing:**
   - Follow DRC rules
   - Add fiducials for assembly
   - Include test points

---

## Resources

### KiCad

- **Website:** [kicad.org](https://www.kicad.org/)
- **Documentation:** [docs.kicad.org](https://docs.kicad.org/)
- **Forum:** [forum.kicad.info](https://forum.kicad.info/)

### PCB Manufacturing

- **JLCPCB:** [jlcpcb.com](https://jlcpcb.com/)
- **PCBWay:** [pcbway.com](https://www.pcbway.com/)
- **OSH Park:** [oshpark.com](https://oshpark.com/)

### Component Suppliers

- **DigiKey:** [digikey.com](https://www.digikey.com/)
- **Mouser:** [mouser.com](https://www.mouser.com/)
- **LCSC:** [lcsc.com](https://www.lcsc.com/)

---

## Summary

### Design Statistics

- **Total boards:** 8 (1 main logic, 1 add/sub, 1 flags, 1 control, 4 LED panels)
- **Total transistors:** 3,856+
- **Total ICs:** 5× 74HC series
- **PCB area:** ~1,200 cm² total
- **Design time:** ~4 weeks
- **Fabrication time:** 1-2 weeks

### Verification Status

- **Schematic ERC:** Pass
- **PCB DRC:** Pass
- **SPICE simulation:** 100% verified
- **Fabrication:** Complete
- **Assembly:** Complete
- **Testing:** 95% verified

---

**For more information:**
- [KiCad Detailed Guide](kicad/README.md)
- [SPICE Simulation Guide](ltspice/README.md)
- [3D Models](../web/README.md)
- [Architecture Documentation](../docs/ARCHITECTURE.md)

---

**Last Updated:** 2026-01-16  
**Version:** 1.0

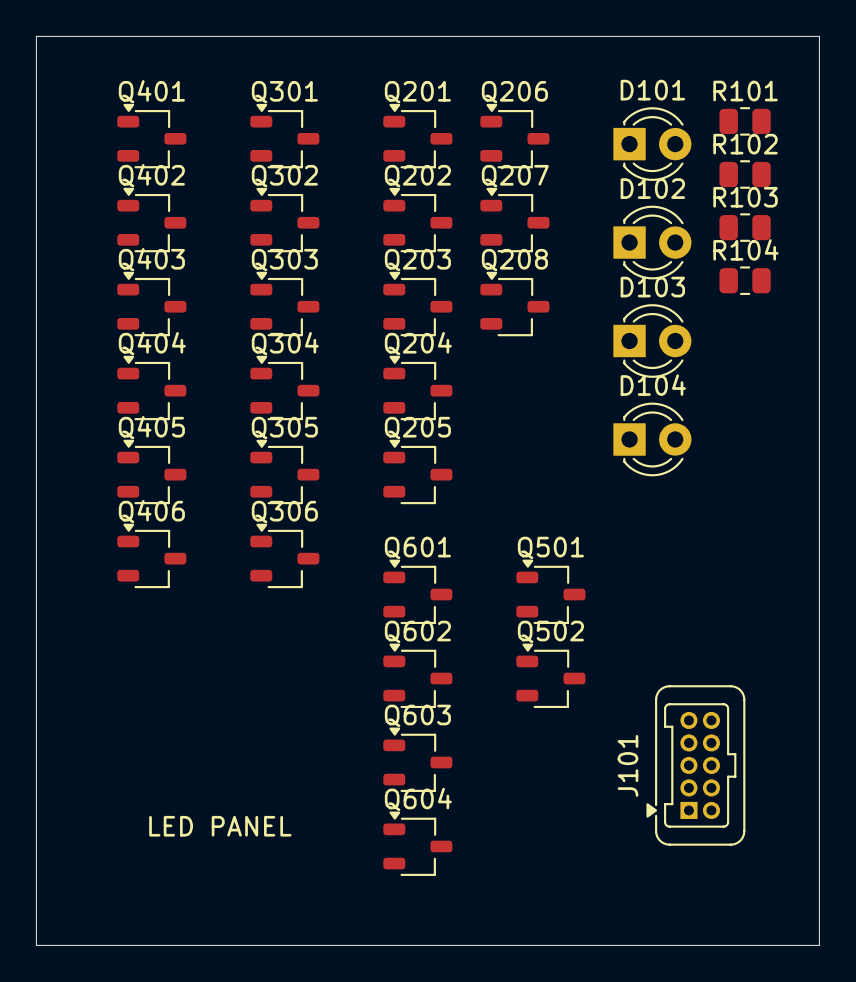
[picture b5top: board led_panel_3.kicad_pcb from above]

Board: 2 copper layers, 43.5 x 50.5 mm, 35 parts (0 on the bottom side), 24 nets, no tracks yet.

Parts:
D101: LED22; LED_D3.0mm
D102: LED21; LED_D3.0mm
D103: LED23; LED_D3.0mm
D104: LED20; LED_D3.0mm
J101: Conn_01x10_Pin; Harwin_Gecko-G125-FVX1005L0X_2x05_P1.25mm_Vertical
Q201, Q202, Q206, Q207, Q302, Q303, Q305, Q402, Q403, Q405, Q501, Q601, Q604: PMOS; TSOT-23
Q203, Q204, Q205, Q208, Q301, Q304, Q306, Q401, Q404, Q406, Q502, Q602, Q603: NMOS; TSOT-23
R101, R102, R103, R104: 300; R_0805_2012Metric

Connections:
/CTRL0: Q202.2 (G), Q204.2 (G)
/CTRL1: Q201.2 (G), Q203.2 (G)
/CTRL2: Q301.2 (G), Q302.2 (G)
/CTRL3: Q303.2 (G), Q304.2 (G)
/CTRL4: Q205.2 (G), Q206.2 (G), Q602.2 (G), Q604.2 (G)
/and2_1/A: Q305.1 (D), Q306.1 (D), Q601.2 (G), Q603.2 (G)
/and2_1/Y: Q403.2 (G), Q404.2 (G), Q501.1 (D), Q502.1 (D)
/and2_1/nand2_1/Y: Q501.2 (G), Q502.2 (G), Q601.1 (D), Q602.1 (D), Q604.1 (D)
/and3_1/Y: Q207.1 (D), Q208.1 (D), Q401.2 (G), Q402.2 (G)
/or2_2/Y: Q405.1 (D), Q406.1 (D), R104.2
GND: D101.1 (K), D102.1 (K), D103.1 (K), D104.1 (K), Q205.3 (S), Q208.3 (S), Q301.3 (S), Q304.3 (S), Q306.3 (S), Q401.3 (S), Q404.3 (S), Q406.3 (S), Q502.3 (S), Q603.3 (S)
unnamed: D101.2 (A), R101.1
unnamed: D102.2 (A), R102.1
unnamed: D103.2 (A), R103.1
unnamed: D104.2 (A), R104.1
unnamed: Q201.1 (D), Q202.1 (D), Q203.1 (D), Q206.1 (D), Q207.2 (G), Q208.2 (G)
unnamed: Q203.3 (S), Q204.1 (D)
unnamed: Q204.3 (S), Q205.1 (D)
unnamed: Q301.1 (D), Q303.1 (D), Q304.1 (D), Q305.2 (G), Q306.2 (G)
unnamed: Q302.1 (D), Q303.3 (S)
unnamed: Q401.1 (D), Q403.1 (D), Q404.1 (D), Q405.2 (G), Q406.2 (G)
unnamed: Q402.1 (D), Q403.3 (S)
unnamed: Q602.3 (S), Q603.1 (D)
VCC: Q201.3 (S), Q202.3 (S), Q206.3 (S), Q207.3 (S), Q302.3 (S), Q305.3 (S), Q402.3 (S), Q405.3 (S), Q501.3 (S), Q601.3 (S), Q604.3 (S)

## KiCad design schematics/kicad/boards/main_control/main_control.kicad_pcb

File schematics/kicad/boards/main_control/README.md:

# Control Decoder Board

**5-bit opcode decoder generating internal control signals**

---

## Function

Decode FUNC[4:0] opcode into internal control signals for ALU operation.

---

## Schematic

*Control unit opcode decoder*

---

## Control Signal Generation

### Decode Table

| FUNC[4:0] | M | MUX_SEL | INV_OUT | LOGIC_SEL |
|-----------|---|---------|---------|-----------|
| 00000 (ADD) | 0 | 0 | 0 | xxx |
| 00001 (SUB) | 1 | 0 | 0 | xxx |
| 01000 (NAND) | x | 1 | 0 | 000 |
| 01101 (AND) | x | 1 | 1 | 000 |

See [docs/OPCODE_TABLE.md](../../../../docs/OPCODE_TABLE.md) for complete table.

---

## Signals

**Inputs:**
- FUNC[4:0] - 5-bit opcode

**Outputs:**
- M - ADD/SUB mode
- MUX_SEL - Arithmetic(0) / Logic(1)
- INV_OUT - Global inversion enable
- LOGIC_SEL[2:0] - Logic operation select

---

## Implementation

**Transistor count:** ~68T

**Combinational decode logic** - no clock required

---

**Last Updated:** 2026-01-16

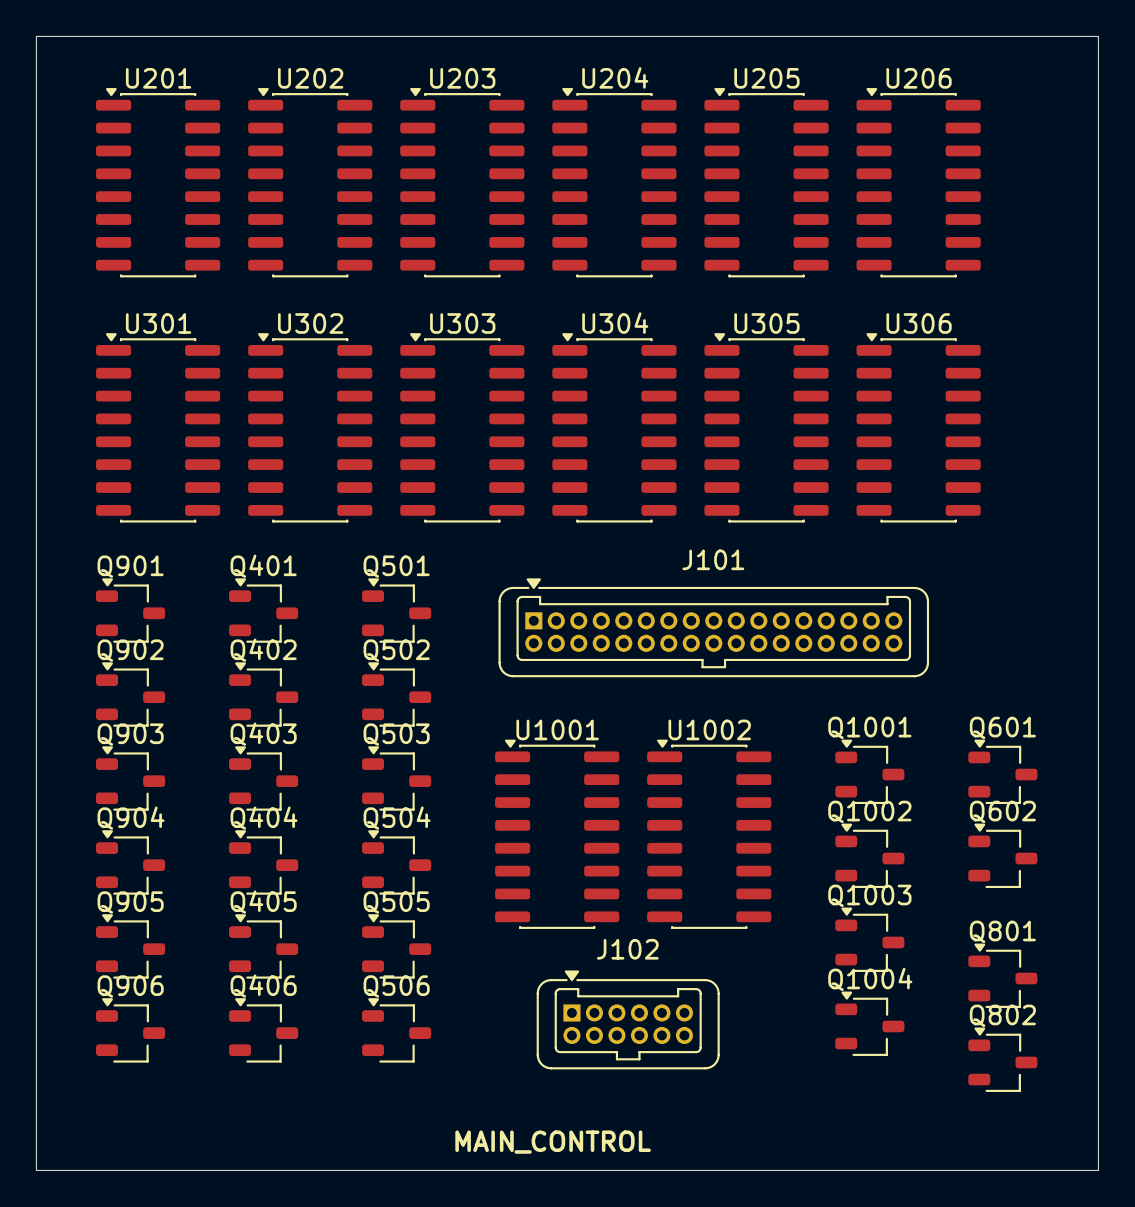
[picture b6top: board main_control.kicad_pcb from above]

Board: 2 copper layers, 59.0 x 63.0 mm, 42 parts (0 on the bottom side), 76 nets, no tracks yet.

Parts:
J101: Conn_01x34_Pin; Harwin_Gecko-G125-FVX3405L0X_2x17_P1.25mm_Vertical
J102: Conn_01x12_Socket; Harwin_Gecko-G125-FVX1205L0X_2x06_P1.25mm_Vertical
Q401, Q404, Q406, Q501, Q504, Q506, Q602, Q802, Q901, Q904, Q906, Q1002, Q1003: NMOS; TSOT-23
Q402, Q403, Q405, Q502, Q503, Q505, Q601, Q801, Q902, Q903, Q905, Q1001, Q1004: PMOS; TSOT-23
U201, U202, U203, U204, U205, U206, U301, U302, U303, U304, U305, U306, U1001, U1002: 74HC157; SOIC-16_3.9x9.9mm_P1.27mm

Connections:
/CMP_NOT_SEL: Q905.1 (D), Q906.1 (D), U1001.1 (S), U1002.1 (S)
/CTRL0: Q903.2 (G), Q904.2 (G), U205.1 (S), U206.1 (S)
/CTRL1: Q901.2 (G), Q902.2 (G), U201.1 (S), U202.1 (S), U203.1 (S), U204.1 (S)
/CTRL2: Q503.2 (G), Q504.2 (G)
/CTRL3: Q403.2 (G), Q404.2 (G), Q801.2 (G), Q802.2 (G)
/CTRL4: Q401.2 (G), Q402.2 (G), Q1001.2 (G), Q1003.2 (G)
/SIG0: Q601.1 (D), Q602.1 (D), U305.1 (S), U306.1 (S)
/SIG1: Q405.1 (D), Q406.1 (D), U301.1 (S), U302.1 (S), U303.1 (S), U304.1 (S)
/W0: U303.3 (I1a), U1001.4 (Za)
/W1: U303.6 (I1b), U1001.7 (Zb)
/W2: U303.10 (I1c), U1001.9 (Zc)
/W3: U303.13 (I1d), U1001.12 (Zd)
/W4: U304.3 (I1a), U1002.4 (Za)
/W5: U304.6 (I1b), U1002.7 (Zb)
/W6: U304.10 (I1c), U1002.9 (Zc)
/W7: U304.13 (I1d), U1002.12 (Zd)
/X0: U205.4 (Za), U301.3 (I1a)
/X1: U205.7 (Zb), U301.6 (I1b)
/X2: U205.9 (Zc), U301.10 (I1c)
/X3: U205.12 (Zd), U301.13 (I1d)
/X4: U206.4 (Za), U302.3 (I1a)
/X5: U206.7 (Zb), U302.6 (I1b)
/X6: U206.9 (Zc), U302.10 (I1c)
/X7: U206.12 (Zd), U302.13 (I1d)
/and2_9/B: Q505.1 (D), Q506.1 (D), Q1002.2 (G), Q1004.2 (G)
/and2_9/nand2_1/Y: Q601.2 (G), Q602.2 (G), Q1001.1 (D), Q1002.1 (D), Q1004.1 (D)
/not_7/Y: Q501.2 (G), Q502.2 (G), Q801.1 (D), Q802.1 (D)
ASR0: U201.3 (I1a), U201.11 (I0c), U203.2 (I0a), U204.10 (I1c)
ASR1: U201.6 (I1b), U201.14 (I0d), U203.5 (I0b), U204.6 (I1b)
ASR2: U201.10 (I1c), U202.2 (I0a), U203.11 (I0c), U204.3 (I1a)
ASR3: U201.13 (I1d), U202.5 (I0b), U203.13 (I1d), U203.14 (I0d)
ASR4: U202.3 (I1a), U202.11 (I0c), U203.10 (I1c), U204.2 (I0a)
ASR5: U202.6 (I1b), U202.14 (I0d), U203.6 (I1b), U204.5 (I0b)
ASR6: U202.10 (I1c), U203.3 (I1a), U204.11 (I0c), U204.14 (I0d)
LSL0: Q401.3 (S), Q404.3 (S), Q406.3 (S), Q501.3 (S), Q504.3 (S), Q506.3 (S), Q602.3 (S), Q802.3 (S), Q901.3 (S), Q904.3 (S), Q906.3 (S), Q1003.3 (S), U201.2 (I0a), U201.8 (GND), U201.15 (E), U202.8 (GND), U202.13 (I1d), U202.15 (E), U203.8 (GND), U203.15 (E), U204.8 (GND), U204.15 (E), U205.8 (GND), U205.15 (E), U206.8 (GND), U206.15 (E), U301.8 (GND), U301.15 (E), U302.8 (GND), U302.15 (E), U303.8 (GND), U303.15 (E), U304.8 (GND), U304.15 (E), U305.8 (GND), U305.15 (E), U306.8 (GND), U306.15 (E), U1001.8 (GND), U1001.15 (E), U1002.8 (GND), U1002.15 (E)
LSL1: U201.5 (I0b), U204.13 (I1d)
unnamed: Q401.1 (D), Q403.1 (D), Q404.1 (D), Q405.2 (G), Q406.2 (G)
unnamed: Q402.1 (D), Q403.3 (S)
unnamed: Q501.1 (D), Q503.1 (D), Q504.1 (D), Q505.2 (G), Q506.2 (G)
unnamed: Q502.1 (D), Q503.3 (S)
unnamed: Q901.1 (D), Q903.1 (D), Q904.1 (D), Q905.2 (G), Q906.2 (G)
unnamed: Q902.1 (D), Q903.3 (S)
unnamed: Q1002.3 (S), Q1003.1 (D)
unnamed: U201.4 (Za), U205.2 (I0a)
unnamed: U201.7 (Zb), U205.5 (I0b)
unnamed: U201.9 (Zc), U205.11 (I0c)
unnamed: U201.12 (Zd), U205.14 (I0d)
unnamed: U202.4 (Za), U205.3 (I1a)
unnamed: U202.7 (Zb), U205.6 (I1b)
unnamed: U202.9 (Zc), U205.10 (I1c)
unnamed: U202.12 (Zd), U205.13 (I1d)
unnamed: U203.4 (Za), U206.2 (I0a)
unnamed: U203.7 (Zb), U206.5 (I0b)
unnamed: U203.9 (Zc), U206.11 (I0c)
unnamed: U203.12 (Zd), U206.14 (I0d)
unnamed: U204.4 (Za), U206.3 (I1a)
unnamed: U204.7 (Zb), U206.6 (I1b)
unnamed: U204.9 (Zc), U206.10 (I1c)
unnamed: U204.12 (Zd), U206.13 (I1d)
unnamed: U301.4 (Za), U305.2 (I0a)
unnamed: U301.7 (Zb), U305.5 (I0b)
unnamed: U301.9 (Zc), U305.11 (I0c)
unnamed: U301.12 (Zd), U305.14 (I0d)
unnamed: U302.4 (Za), U305.3 (I1a)
unnamed: U302.7 (Zb), U305.6 (I1b)
unnamed: U302.9 (Zc), U305.10 (I1c)
unnamed: U302.12 (Zd), U305.13 (I1d)
unnamed: U303.4 (Za), U306.2 (I0a)
unnamed: U303.7 (Zb), U306.5 (I0b)
unnamed: U303.9 (Zc), U306.11 (I0c)
unnamed: U303.12 (Zd), U306.14 (I0d)
unnamed: U304.4 (Za), U306.3 (I1a)
unnamed: U304.7 (Zb), U306.6 (I1b)
unnamed: U304.9 (Zc), U306.10 (I1c)
unnamed: U304.12 (Zd), U306.13 (I1d)
VCC: Q402.3 (S), Q405.3 (S), Q502.3 (S), Q505.3 (S), Q601.3 (S), Q801.3 (S), Q902.3 (S), Q905.3 (S), Q1001.3 (S), Q1004.3 (S), U201.16 (VCC), U202.16 (VCC), U203.16 (VCC), U204.16 (VCC), U205.16 (VCC), U206.16 (VCC), U301.16 (VCC), U302.16 (VCC), U303.16 (VCC), U304.16 (VCC), U305.16 (VCC), U306.16 (VCC), U1001.16 (VCC), U1002.16 (VCC)
